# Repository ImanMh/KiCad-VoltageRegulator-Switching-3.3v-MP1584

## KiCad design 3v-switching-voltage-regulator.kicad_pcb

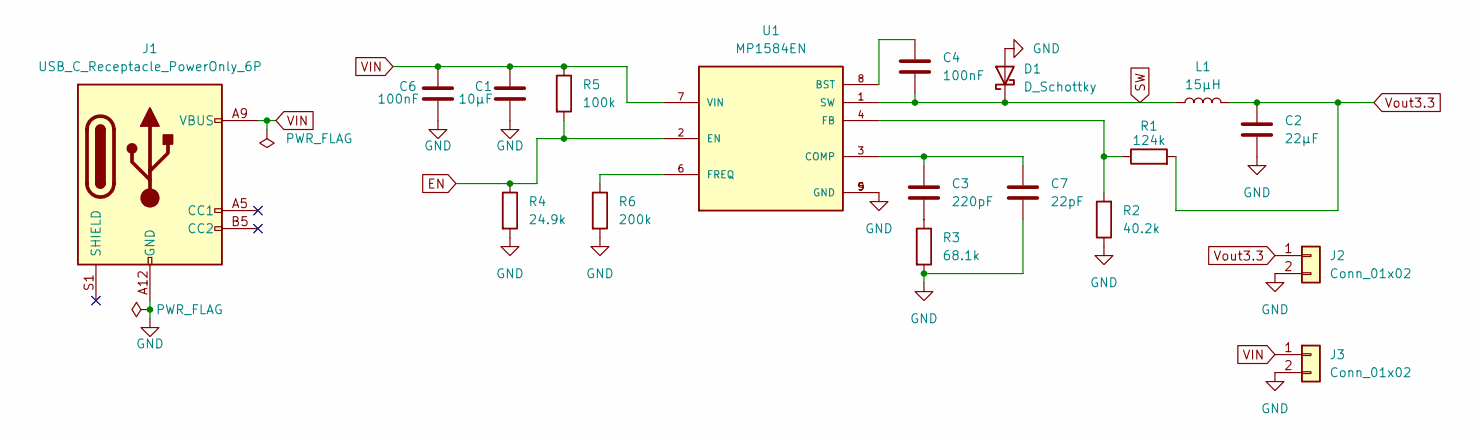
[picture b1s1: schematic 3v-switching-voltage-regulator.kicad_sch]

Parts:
C1: 10µF; C_1206_3216Metric
C2: 22µF; C_1206_3216Metric
C3: 220pF; C_1206_3216Metric
C4, C6: 100nF; C_1206_3216Metric
C7: 22pF; C_1206_3216Metric
D1: D_Schottky; D_1206_3216Metric
J1: USB_C_Receptacle_PowerOnly_6P; USB_C_Receptacle_GCT_USB4125-xx-x-0190_6P_TopMnt_Horizontal
J2, J3: Conn_01x02; PinHeader_1x02_P2.54mm_Vertical
L1: 15µH; L_APV_APH1040
R1: 124k; R_1206_3216Metric
R2: 40.2k; R_1206_3216Metric
R3: 68.1k; R_1206_3216Metric
R4: 24.9k; R_1206_3216Metric
R5: 100k; R_1206_3216Metric
R6: 200k; R_1206_3216Metric
U1: MP1584EN; SOIC127P600X170-9N

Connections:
EN: R4.1, R5.2, U1.2 (EN)
GND: C1.2, C2.2, C6.2, C7.2, D1.2 (A), J1.A12 (GND), J1.B12 (GND), J2.2, J3.2, R2.1, R3.2, R4.2, R6.2, U1.5 (GND), U1.9 (GND); also elsewhere on the board
unnamed: C3.2, R3.1
unnamed: C4.1, U1.8 (BST)
unnamed: C3.1, C7.1, U1.3 (COMP)
unnamed: R1.1, R2.2, U1.4 (FB)
unnamed: R6.1, U1.6 (FREQ)
SW: C4.2, D1.1 (K), L1.1, U1.1 (SW)
VIN: C1.1, C6.1, J1.A9 (VBUS), J1.B9 (VBUS), J3.1, R5.1, U1.7 (VIN); also elsewhere on the board
Vout3.3: C2.1, J2.1, L1.2, R1.2

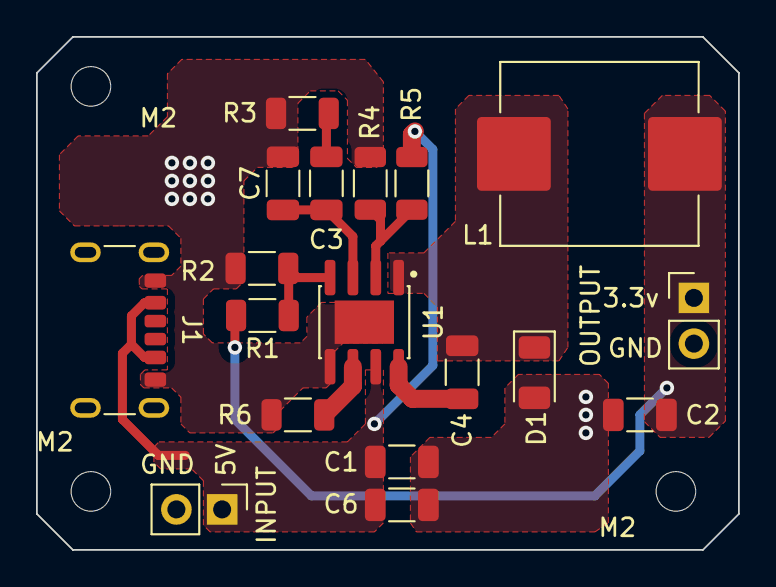
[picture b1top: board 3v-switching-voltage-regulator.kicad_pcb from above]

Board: 2 copper layers, 39.0 x 28.5 mm, 21 parts (0 on the bottom side), 10 nets.

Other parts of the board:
INPUT: Conn_01x02; PinHeader_1x02_P2.54mm_Vertical
M2, M2#2, M2#3: MountingHole_2.2mm_M2

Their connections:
GND: INPUT.2; also elsewhere on the board
VIN: INPUT.1; also elsewhere on the board

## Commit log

2025-10-19 v1 initial commit
2025-10-19 reduces board size and adds input output connections
2025-10-19 generats fabrication files for JLCPCB
